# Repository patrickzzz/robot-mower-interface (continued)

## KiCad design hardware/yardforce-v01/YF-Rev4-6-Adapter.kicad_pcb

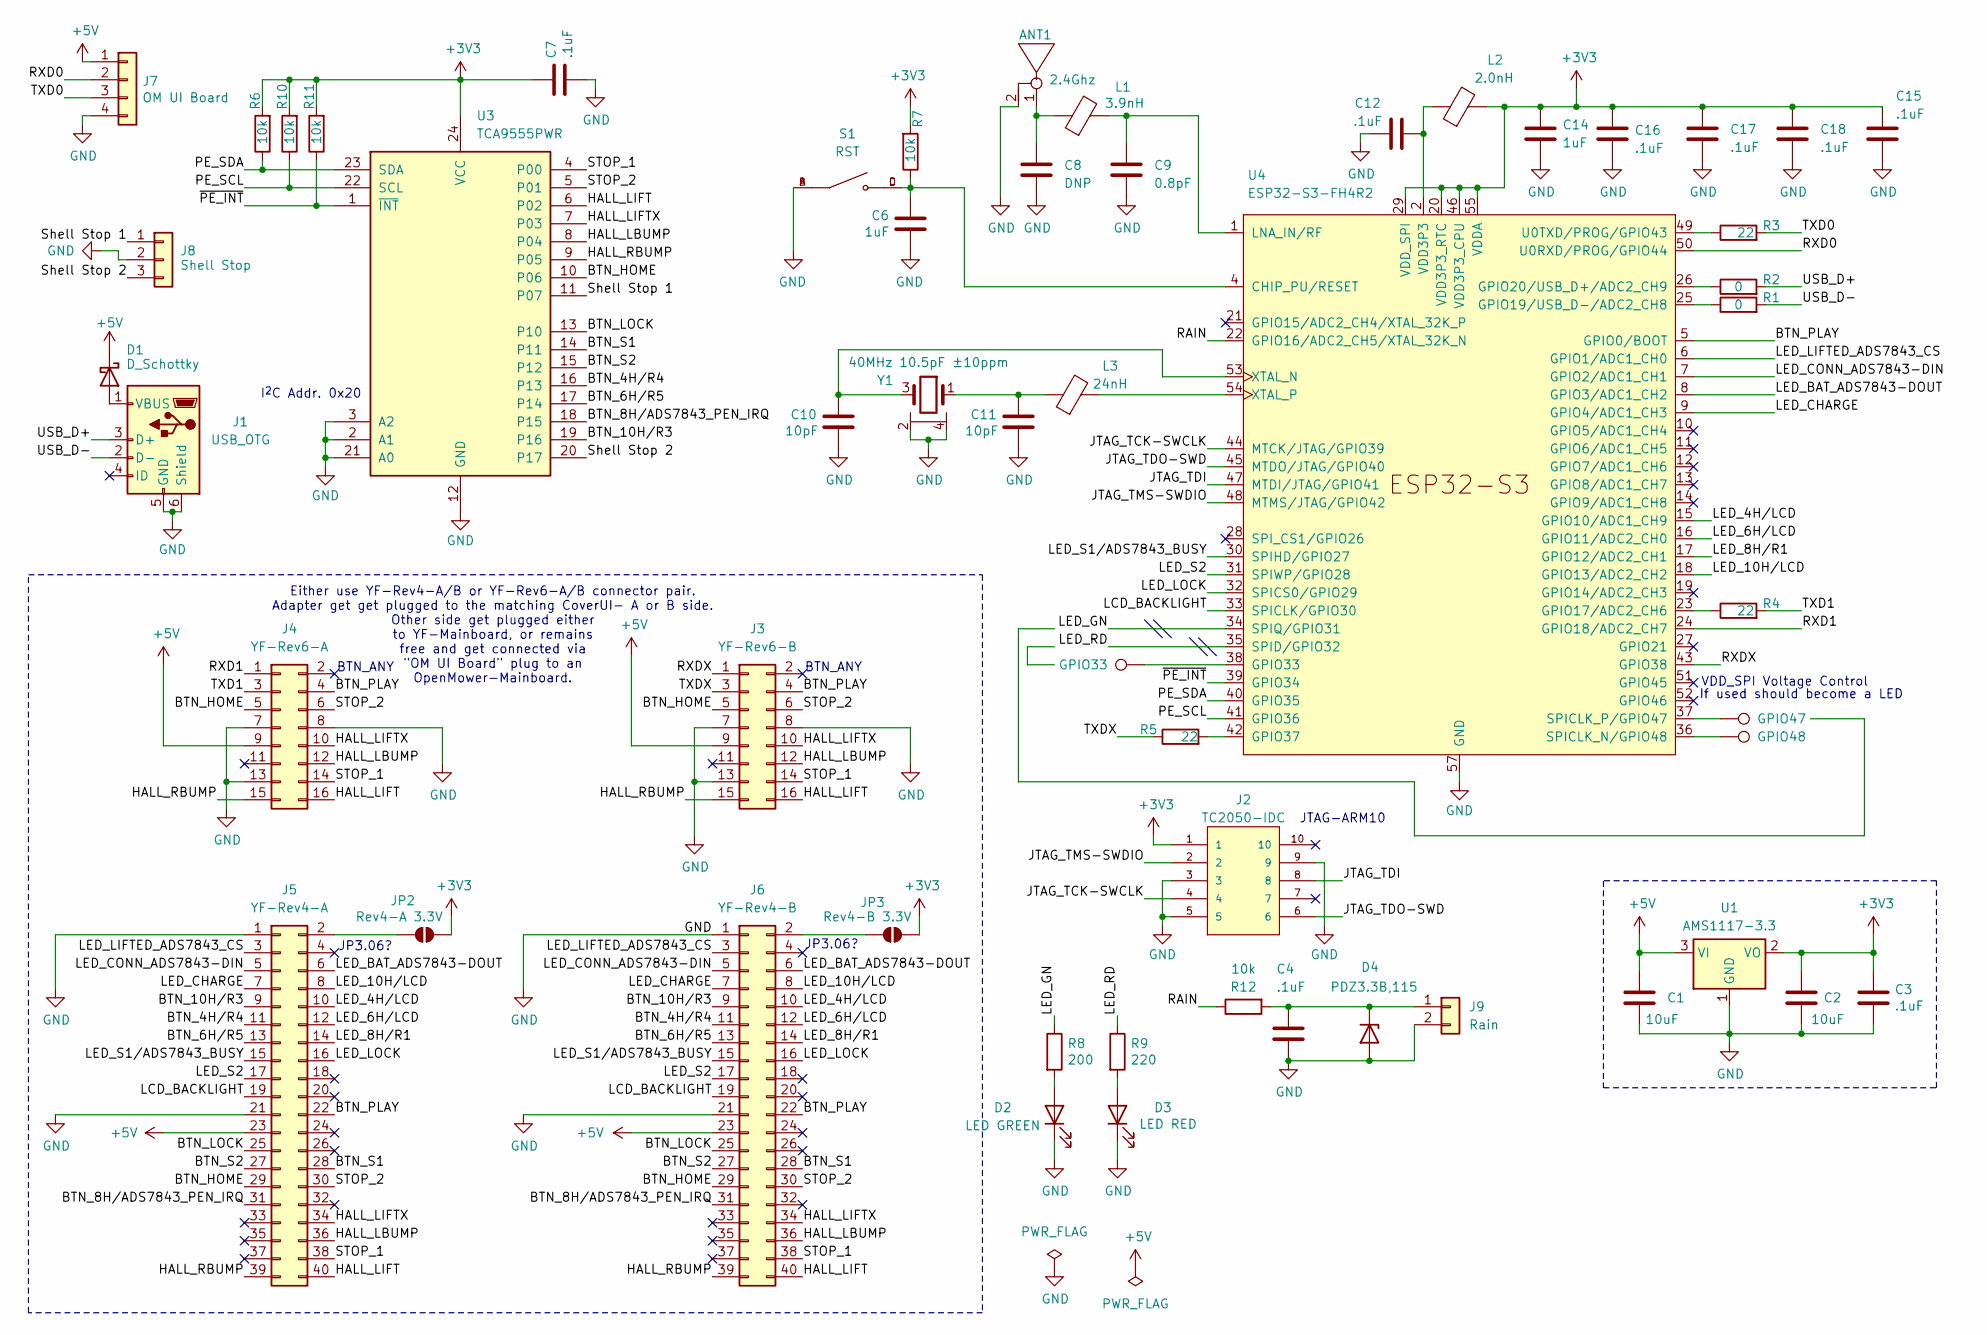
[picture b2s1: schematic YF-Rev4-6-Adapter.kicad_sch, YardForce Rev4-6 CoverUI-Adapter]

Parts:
ANT1: 2.4Ghz; PCB_Antenna_2.4GHz_Left
C1, C2: 10uF; C_0603_1608Metric; LCSC C19702
C3, C7, C12, C15, C16, C17, C18: .1uF; C_0402_1005Metric; LCSC C1525
C4: .1uF; C_0402_1005Metric; JLC C307331
C6, C14: 1uF; C_0402_1005Metric; LCSC C52923
C8: DNP; C_0402_1005Metric
C9: 0.8pF; C_0402_1005Metric; LCSC C5448872
C10, C11: 10pF; C_0402_1005Metric; MFR Part 0402CG140J500NT; LCSC C32949
D1: D_Schottky; D_SOD-123; Part Number PMEG2010ER,115; Digikey 1727-5192-1-ND
D2: LED GREEN; LED_0603_1608Metric; Part Number LTST-C191KGKT; Digikey 160-1446-1-ND
D3: LED RED; LED_0603_1608Metric; Part Number LTST-C191KRKT; Digikey 160-1447-1-ND
D4: PDZ3.3B,115; D_SOD-323; JLC C426855
GPIO33, GPIO47, GPIO48: TestPoint; TestPoint_Pad_1.0x1.0mm
J1: USB_OTG; USB_Micro-B_Wuerth_614105150721_Vertical; LCSC C668588
J2: TC2050-IDC; TAG-CONNECT_TC2050-IDC; PARTREV A
J3: YF-Rev6-B; IDC-Hybrid_2x08_P2.54mm_Latch_Vertical; DigiKey S9196-ND
J4: YF-Rev6-A; IDC-Hybrid_2x08_P2.54mm_Latch_Vertical; DigiKey S9196-ND
J5: YF-Rev4-A; IDC-Hybrid_2x20_P2.54mm_Latch_Vertical; DigiKey SFH11-PBPC-D20-ST-BK
J6: YF-Rev4-B; IDC-Hybrid_2x20_P2.54mm_Latch_Vertical; DigiKey SFH11-PBPC-D20-ST-BK
J7: OM UI Board; JST_XH_B4B-XH-A_1x04_P2.50mm_Vertical; Part Number B4B-XH-A(LF)(SN); Digikey 455-2249-ND
J8: Shell Stop; JST_XH_B3B-XH-A_1x03_P2.50mm_Vertical; Part Number B3B-XH-A(LF)(SN); LCSC C144394
J9: Rain; JST_XH_B2B-XH-A_1x02_P2.50mm_Vertical; Part Number B2B-XH-A-GU; Digikey 455-2946-ND
JP2: Rev4-A 3.3V; SolderJumper-2_P1.3mm_Open_RoundedPad1.0x1.5mm
JP3: Rev4-B 3.3V; SolderJumper-2_P1.3mm_Open_RoundedPad1.0x1.5mm
L1: 3.9nH; L_0402_1005Metric; LCSC C370223
L2: 2.0nH; L_0402_1005Metric; LCSC C963978
L3: 24nH; L_0402_1005Metric; MFR Part SDCL1005C24NJTDF; LCSC C401493
R1, R2: 0; R_0402_1005Metric; LCSC C17168
R3, R4, R5: 22; R_0603_1608Metric; LCSC C23345
R6, R7, R10, R11: 10k; R_0603_1608Metric; LCSC C25804
R8: 200; R_0603_1608Metric; LCSC C8218
R9: 220; R_0603_1608Metric; LCSC C22962
R12: 10k; R_0603_1608Metric; JLC C25744
S1: RST; SW_TS-1187A-B-A-B; PARTREV A0; LCSC C318884
U1: AMS1117-3.3; SOT-223-3_TabPin2; LCSC C6186
U3: TCA9555PWR; TSSOP-24_4.4x7.8mm_P0.65mm; LCSC C465732
U4: ESP32-S3-FH4R2; QFN-56-1EP_7x7mm_P0.4mm_EP4x4mm_ThermalVias; LCSC C3013940
Y1: 40MHz 10.5pF ±10ppm; Crystal_SMD_2016-4Pin_2.0x1.6mm; MF Part K2B4000010510; LCSC C18209006

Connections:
+3V3: C2.1, C3.1, C7.1, C14.1, C15.1, C16.1, C17.1, C18.1, J2.1, JP2.2 (B), JP3.2 (B), L2.2, R6.2, R7.2, R10.2, R11.2, U1.2 (VO), U3.24 (VCC), U4.20 (VDD3P3_RTC), U4.29 (VDD_SPI), U4.46 (VDD3P3_CPU), U4.55 (VDDA), U4.56 (VDDA)
+5V: C1.1, D1.1 (K), J3.9, J4.9, J5.23, J6.23, J7.1, U1.3 (VI)
/BTN_4H/R4: J5.11, J6.11, U3.16 (P13)
/BTN_6H/R5: J5.13, J6.13, U3.17 (P14)
/BTN_8H/ADS7843_PEN_IRQ: J5.31, J6.31, U3.18 (P15)
/BTN_10H/R3: J5.9, J6.9, U3.19 (P16)
/BTN_HOME: J3.5, J4.5, J5.29, J6.29, U3.10 (P06)
/BTN_LOCK: J5.25, J6.25, U3.13 (P10)
/BTN_PLAY: J3.4, J4.4, J5.22, J6.22, U4.5 (GPIO0/BOOT)
/BTN_S1: J5.28, J6.28, U3.14 (P11)
/BTN_S2: J5.27, J6.27, U3.15 (P12)
/HALL_LBUMP: J3.12, J4.12, J5.36, J6.36, U3.8 (P04)
/HALL_LIFT: J3.16, J4.16, J5.40, J6.40, U3.6 (P02)
/HALL_LIFTX: J3.10, J4.10, J5.34, J6.34, U3.7 (P03)
/HALL_RBUMP: J3.15, J4.15, J5.39, J6.39, U3.9 (P05)
/JTAG_TCK-SWCLK: J2.4, U4.44 (MTCK/JTAG/GPIO39)
/JTAG_TDI: J2.8, U4.47 (MTDI/JTAG/GPIO41)
/JTAG_TDO-SWD: J2.6, U4.45 (MTDO/JTAG/GPIO40)
/JTAG_TMS-SWDIO: J2.2, U4.48 (MTMS/JTAG/GPIO42)
/LCD_BACKLIGHT: J5.19, J6.19, U4.33 (SPICLK/GPIO30)
/LED_4H/LCD: J5.10, J6.10, U4.15 (GPIO10/ADC1_CH9)
/LED_6H/LCD: J5.12, J6.12, U4.16 (GPIO11/ADC2_CH0)
/LED_8H/R1: J5.14, J6.14, U4.17 (GPIO12/ADC2_CH1)
/LED_10H/LCD: J5.8, J6.8, U4.18 (GPIO13/ADC2_CH2)
/LED_BAT_ADS7843-DOUT: J5.6, J6.6, U4.8 (GPIO3/ADC1_CH2)
/LED_CHARGE: J5.7, J6.7, U4.9 (GPIO4/ADC1_CH3)
/LED_CONN_ADS7843-DIN: J5.5, J6.5, U4.7 (GPIO2/ADC1_CH1)
/LED_GN: R8.1, U4.34 (SPIQ/GPIO31)
/LED_LIFTED_ADS7843_CS: J5.3, J6.3, U4.6 (GPIO1/ADC1_CH0)
/LED_LOCK: J5.16, J6.16, U4.32 (SPICS0/GPIO29)
/LED_RD: R9.1, U4.35 (SPID/GPIO32)
/LED_S1/ADS7843_BUSY: J5.15, J6.15, U4.30 (SPIHD/GPIO27)
/LED_S2: J5.17, J6.17, U4.31 (SPIWP/GPIO28)
/PE_SCL: R10.1, U3.22 (SCL), U4.41 (GPIO36)
/PE_SDA: R6.1, U3.23 (SDA), U4.40 (GPIO35)
/RAIN: R12.1, U4.22 (GPIO16/ADC2_CH5/XTAL_32K_N)
/RXD0: J7.2, U4.50 (U0RXD/PROG/GPIO44)
/RXD1: J4.1, U4.24 (GPIO18/ADC2_CH7)
/RXDX: J3.1, U4.43 (GPIO38)
/STOP_1: J3.14, J4.14, J5.38, J6.38, U3.4 (P00)
/STOP_2: J3.6, J4.6, J5.30, J6.30, U3.5 (P01)
/Shell Stop 1: J8.1, U3.11 (P07)
/Shell Stop 2: J8.3, U3.20 (P17)
/TXD0: J7.3, R3.2
/TXD1: J4.3, R4.2
/TXDX: J3.3, R5.1
/USB_D+: J1.3 (D+), R2.2
/USB_D-: J1.2 (D-), R1.2
/~PE_INT: R11.1, U3.1 (~INT), U4.39 (GPIO34)
GND: ANT1.2, C1.2, C2.2, C3.2, C4.2, C6.2, C7.2, C8.2, C9.2, C10.2, C11.2, C12.1, C14.2, C15.2, C16.2, C17.2, C18.2, D2.1 (K), D3.1 (K), D4.2 (A), J1.5 (GND), J1.6 (Shield), J2.3, J2.5, J2.9, J3.7, J3.8, J3.13, J4.7, J4.8, J4.13, J5.1, J5.21, J6.1, J6.21, J7.4, J8.2, J9.2, S1.A, S1.B, U1.1 (GND), U3.2 (A1), U3.3 (A2), U3.12 (GND), U3.21 (A0), U4.57 (GND), Y1.2, Y1.4
unnamed: ANT1.1, C8.1, L1.1
unnamed: C11.1, L3.1, Y1.1
unnamed: D1.2 (A), J1.1 (VBUS)
unnamed: D2.2 (A), R8.2
unnamed: D3.2 (A), R9.2
unnamed: C4.1, D4.1 (K), J9.1, R12.2
unnamed: J5.2, JP2.1 (A)
unnamed: J6.2, JP3.1 (A)
unnamed: C6.1, R7.1, S1.C, S1.D, U4.4 (CHIP_PU/RESET)
unnamed: R4.1, U4.23 (GPIO17/ADC2_CH6)
unnamed: R1.1, U4.25 (GPIO19/USB_D-/ADC2_CH8)
unnamed: R2.1, U4.26 (GPIO20/USB_D+/ADC2_CH9)
unnamed: GPIO33.1, U4.38 (GPIO33)
unnamed: R5.2, U4.42 (GPIO37)
unnamed: C9.1, L1.2, U4.1 (LNA_IN/RF)
unnamed: GPIO48.1, U4.36 (SPICLK_N/GPIO48)
unnamed: GPIO47.1, U4.37 (SPICLK_P/GPIO47)
unnamed: R3.1, U4.49 (U0TXD/PROG/GPIO43)
unnamed: C10.1, U4.53 (XTAL_N), Y1.3
unnamed: L3.2, U4.54 (XTAL_P)
VDD3P3: C12.2, L2.1, U4.2 (VDD3P3), U4.3 (VDD3P3)

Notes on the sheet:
VDD_SPI Voltage Control
If used should become a LED
JTAG-ARM10
BTN_ANY
JP3.06?
Either use YF-Rev4-A/B or YF-Rev6-A/B connector pair. Adapter get get plugged to the matching CoverUI- A or B side. Other side get plugged either to YF-Mainboard, or remains free and get connected via "OM UI Board" plug to an OpenMower-Mainboard.
I^{2}C Addr. 0x20

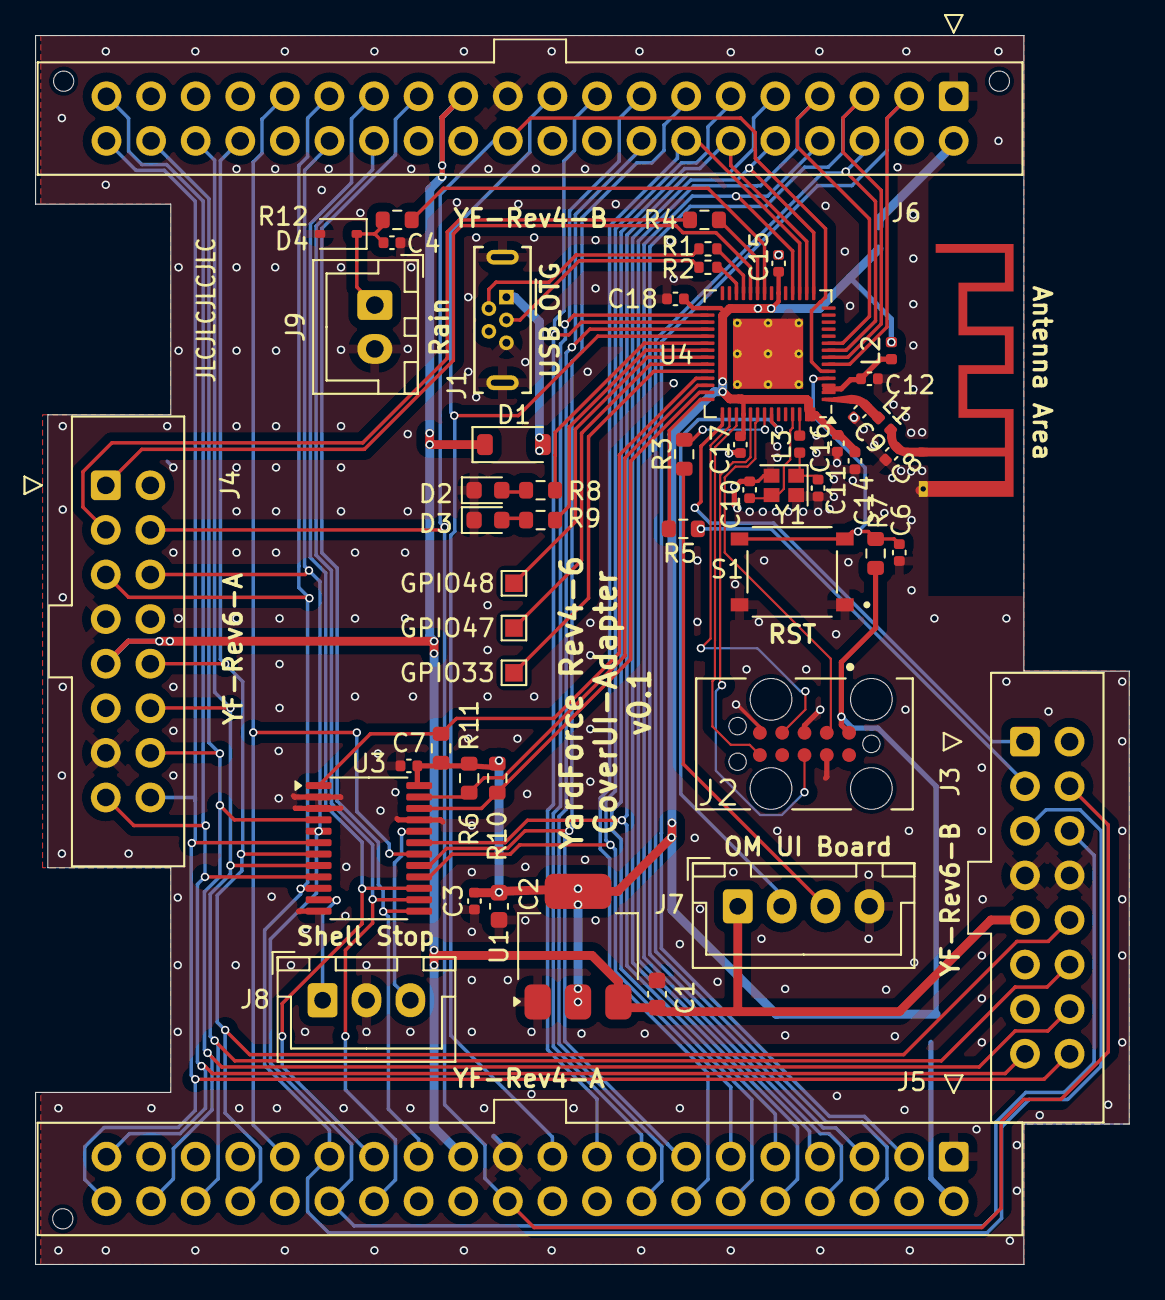
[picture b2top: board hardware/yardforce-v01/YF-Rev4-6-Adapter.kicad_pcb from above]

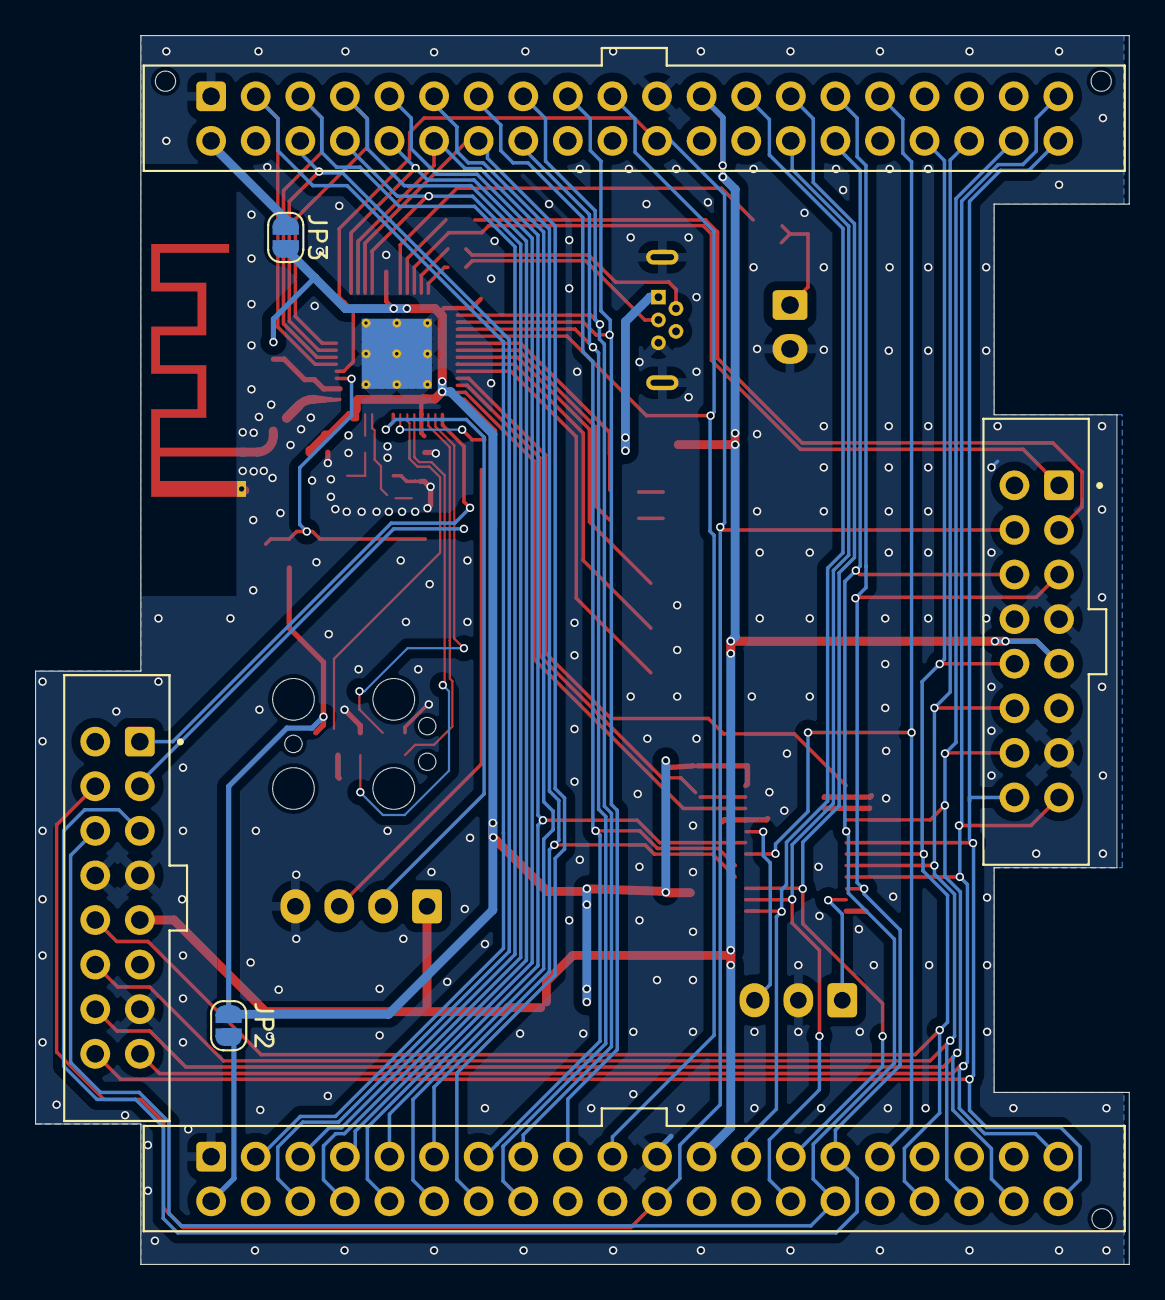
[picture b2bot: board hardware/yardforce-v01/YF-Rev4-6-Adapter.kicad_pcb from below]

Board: 2 copper layers, 62.3 x 70.0 mm, 55 parts (2 on the bottom side), 71 nets.

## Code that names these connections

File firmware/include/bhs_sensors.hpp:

/* Created by Apehaenger on 2024-12-02.
 * Copyright (c) 2024 Jörg Ebeling. All rights reserved.
 *
 * This file is part of the robot-interface project at https://github.com/patrickzzz/robot-interface.
 *
 * This work is licensed under a Creative Commons Attribution-NonCommercial-ShareAlike 4.0 International License.
 *
 * Feel free to use the design in your private/educational projects, but don't try to sell the design or products based on it without getting our consent first.
 *
 * THE SOFTWARE IS PROVIDED "AS IS", WITHOUT WARRANTY OF ANY KIND, EXPRESS OR
 * IMPLIED, INCLUDING BUT NOT LIMITED TO THE WARRANTIES OF MERCHANTABILITY,
 * FITNESS FOR A PARTICULAR PURPOSE AND NONINFRINGEMENT. IN NO EVENT SHALL THE
 * AUTHORS OR COPYRIGHT HOLDERS BE LIABLE FOR ANY CLAIM, DAMAGES OR OTHER
 * LIABILITY, WHETHER IN AN ACTION OF CONTRACT, TORT OR OTHERWISE, ARISING FROM,
 * OUT OF OR IN CONNECTION WITH THE SOFTWARE OR THE USE OR OTHER DEALINGS IN THE
 * SOFTWARE.
 */
#pragma once

#include <esp_log.h>
#include <freertos/queue.h>
#include <inttypes.h>

#include "config.h"
#include "esp_io_expander_tca95xx_16bit/include/esp_io_expander_tca95xx_16bit.h"
#include "I2CManager.hpp"
#include "pins.h"

extern LedSequencer led_red_seq;

/**
 * @brief Button-Hall-Switch Sensors, handle all of those input sensors like:
 * - User Button on the CoverUI
 * - Hall Switches connected to the CoverUI
 * - Normal switches like Stop-Switches on the CoverUI or the Adapter-PCB
 *
 * All input signals get debounced before processed!
 */
namespace bhs_sensors {

// For efficiency and simplicity port expanders input value get assigned 1:1 to a bitfields struct (+ the mapped GPIO play button)
struct State {
#ifdef HW_0_1_X
    bool stop_1 : 1;        // 2 pin plug @ CoverUI. Fit with back-handle plug of one side
    bool stop_2 : 1;        // 2 pin plug @ CoverUI. Fit with back-handle plug of the other side
    bool lift : 1;          // Hall (lift) sensor
    bool lift_x : 1;        // Hall (lift2) sensor
    bool bump_l : 1;        // Hall (bumper) sensor
    bool bump_r : 1;        // Hall (bumper2) sensor
    bool btn_home : 1;      // CoverUI button
    bool shell_stop_1 : 1;  // Shell Stop Plug J8 (pin 1-2) on adapter PCB
    bool btn_lock : 1;      // CoverUI button
    bool btn_s1 : 1;        // CoverUI button
    bool btn_s2 : 1;        // CoverUI button
    // Same as with the "hr" LEDs. If a CoverUI has "hr" buttons, it has 4 of them, but their value is model specific
    bool btn_hr_14 : 1;     // CoverUI button
    bool btn_hr_24 : 1;     // CoverUI button
    bool btn_hr_34 : 1;     // CoverUI button
    bool btn_hr_44 : 1;     // CoverUI button
    bool shell_stop_2 : 1;  // Shell Stop Plug J8 (pin 2-3) on adapter PCB
    // GPIO button inputs get MSB prefixed to TCA9555 inputs
    bool btn_play : 1;  // CoverUI button
#elif HW_0_2_X
    bool stop_2 : 1;        // 2 pin plug @ CoverUI. Fit with back-handle plug of the other side
    bool lift_x : 1;        // Hall (lift2) sensor
    bool bump_l : 1;        // Hall (bumper) sensor
    bool stop_1 : 1;        // 2 pin plug @ CoverUI. Fit with back-handle plug of one side
    bool bump_r : 1;        // Hall (bumper2) sensor
    bool lift : 1;          // Hall (lift) sensor
    bool shell_stop_1 : 1;  // Shell Stop Plug J8 (pin 1-2) on adapter PCB
    bool shell_stop_2 : 1;  // Shell Stop Plug J8 (pin 2-3) on adapter PCB
    // Same as with the "hr" LEDs. If a CoverUI has "hr" buttons, it has 4 of them, but their value is model specific
    bool btn_hr_14 : 1;   // CoverUI button
    bool btn_hr_24 : 1;   // CoverUI button
    bool btn_hr_34 : 1;   // CoverUI button
    bool btn_hr_44 : 1;   // CoverUI button
    bool btn_lock : 1;    // CoverUI button
    bool btn_s2 : 1;      // CoverUI button
    bool btn_s1 : 1;      // CoverUI button
    bool btn_unused : 1;  // Unused TCA input
    // GPIO button inputs get MSB prefixed to TCA9555 inputs
    bool btn_play : 1;  // CoverUI button
    bool btn_home : 1;  // CoverUI button
#else
#error No hardware version HW_x_y_z defined
#endif
};

const char *TAG = "bhs_sensors";

// A typical bounce time is between 2ms up to 10ms.
// To be on the save side, the result of taskCycle * numDebounceStates should be larger
constexpr TickType_t taskCycle = 5;
constexpr uint8_t numDebounceStates = 6;

namespace {  // Anonymous private namespace

// Port expander vars
//static i2c_master_bus_handle_t i2c_handle_ = NULL;
static esp_io_expander_handle_t io_expander_ = NULL;

// BHS states
union StateU {
    uint32_t raw;
    State state;
};
static StateU state_debounced_;  // Current state of debounced BHS sensors

}  // namespace

/**
 * @brief Initialize GPIOs and I2C interfaces
 *
 * @return esp_err_t
 */
esp_err_t init(SystemHealth &sys_health) {
    ESP_LOGI(TAG, "init()");

/*
    // Init I2C for TCA9555 port expander
    const i2c_master_bus_config_t bus_config = {
        .i2c_port = I2C_NUM_0,
        .sda_io_num = portExpSDA,
        .scl_io_num = portExpSCL,
        .clk_source = I2C_CLK_SRC_DEFAULT,
        .glitch_ignore_cnt = 7,
        .intr_priority = 0,
        .trans_queue_depth = 0,
        .flags = {.enable_internal_pullup = 1}};
    if (esp_err_t ret = i2c_new_master_bus(&bus_config, &i2c_handle_) != ESP_OK) {
        ESP_LOGW(TAG, "I2C init failed with error: %s", esp_err_to_name(ret));
        return ret;
    }
    sys_health.port_expander_i2c = true;

    // Init TCA9555 port expander
    if (esp_err_t ret = esp_io_expander_new_i2c_tca95xx_16bit(i2c_handle_, ESP_IO_EXPANDER_I2C_TCA9555_ADDRESS_000, &io_expander_) != ESP_OK) {
        ESP_LOGW(TAG, "Port expander connect failed with error: %s", esp_err_to_name(ret));
        return ret;
    }

    if (esp_err_t ret = esp_io_expander_set_dir(io_expander_, portExpBtnPinMask, IO_EXPANDER_INPUT) != ESP_OK) {
        ESP_LOGW(TAG, "Port expander 'set direction' failed with error: %s", esp_err_to_name(ret));
        return ret;
    }

 */
    io_expander_ = I2CManager::getInstance().getIoExpander();
    sys_health.port_expander = true;

    esp_io_expander_print_state(io_expander_);

    // Play button on normal GPIO
    gpio_config_t gpio_conf = {
        .pin_bit_mask = (1ULL << pinButtonPlay),
        .mode = GPIO_MODE_INPUT,
        .pull_up_en = GPIO_PULLUP_ENABLE,
        .pull_down_en = GPIO_PULLDOWN_DISABLE,
        .intr_type = GPIO_INTR_DISABLE};
    gpio_config(&gpio_conf);

    return ESP_OK;
}

/**
 * @brief Return (debounced) State bitfield for any button, hall or switch.
 * @return State
 */
State getState() {
    return state_debounced_.state;
}

/**
 * @brief Has to get called regulary i.e. by timer or task (approx. 5ms).
 * Store the (button, hall and switch) GPIO states within states_ array and debounces em.
 */
void task(void *arg) {
    static uint32_t states_[numDebounceStates];  // GPIO port state recorder for every taskCycle time interval
    static uint8_t state_index_ = 0;             // Index for next states_ store positions
    // uint32_t state_changed_;                  // Just changed buttons. Might be used if button events are required

    while (1) {
        uint32_t val = 0;
        // Get port expander buttons
        if (esp_err_t ret = esp_io_expander_get_level(io_expander_, portExpBtnPinMask, &val) == ESP_OK) {
            states_[state_index_] = val ^ 0xffff;  // XOR for active-low buttons
        } else {
            led_red_seq.blink({.on_ms = 100, .off_ms = 100, .limit_blink_cycles = 1, .fulfill = true});  // One quick red flash indicate a communication error;
            ESP_LOGW(TAG, "Port expander read failed with error: %s", esp_err_to_name(ret));
        }

        // Add mergeable button(s)
#ifdef HW_0_1_X
        states_[state_index_] |= (gpio_get_level(pinButtonPlay) ? 0 : (uint32_t)mergedExpPinBtnPlay);
#elif HW_0_2_X
        states_[state_index_] |= (gpio_get_level(pinButtonPlay) ? 0 : (uint32_t)mergedExpPinBtnPlay) | (gpio_get_level(pinButtonHome) ? 0 : (uint32_t)mergedExpPinBtnHome);
#else
#error No hardware version HW_x_y_z defined
#endif

        // Debounce
        // uint32_t laststate_debounced_ = state_debounced_.raw;
        unsigned int i;
        for (i = 0, state_debounced_.raw = 0xffffffff; i < numDebounceStates; i++)
            state_debounced_.raw &= states_[i];

        /* AH20241204 Could be used for BHS event trigger of changed BHS sensors
        // Save what changed
        state_changed_ = state_debounced_ ^ laststate_debounced_.raw; */

        // Circular buffer index
        state_index_++;
        if (state_index_ >= numDebounceStates)
            state_index_ = 0;

        vTaskDelay(taskCycle / portTICK_PERIOD_MS);
    }
}

}  // namespace bhs_sensors

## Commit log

2024-10-27 Several changes for v0.2.0 (see CHANGELOG.md)
2024-10-28 Changes to avoid watchdog timer problems: serve static files gzip compressed + increase timeout
2024-10-28 New gzipped webinterface
2024-10-28 Automatically reconnect if Wifi connection is lost
2024-10-28 Ability to do Firmware updates over the air (OTA)
2024-11-03 Minor improvements
2024-11-11 Fix ERC issues
2024-11-12 Add Rev4 3V3 solder jumper
2024-11-12 Fix DRC issues
2024-11-12 BOM Update
2024-11-24 Add HW Prototype v0.1
2024-11-25 Change Micro-USB part to U255-051N-4BH70-SS
2024-11-25 Fix compile error
2024-12-04 Add test-prototype sandbox/example ESP-IDF code
2024-12-04 Add HW v0.1 files and manual mods
2024-12-06 Correct image names
2024-12-06 Finalization of test-prototype
2024-12-27 Don't truncate logs on every startup Correct loading of mowing plan on boot up
2024-12-28 Rev 0.2 hardware
2024-12-28 Add modes of operation overview
2024-12-28 Correct header
2025-01-13 Add mainboard-immitator based on ESP IDF for testing purposes
2025-01-14 Copy of test-prototype, containing a first class to speak to YF CoverUI
2025-01-15 Beginning of LED State manager class
2025-01-16 Add HW comment
2025-01-16 Add HW_0_2_X support for test-prototype
2025-01-16 Add UART pins and baud
2025-01-16 Release v0.2 prototype
2025-01-18 Test for 40 Pin
2025-01-18 initial commit of protoype 2 (wip)
2025-01-19 First PoC
2025-01-20 WIP, Start v2 hardware
2025-01-21 Current state, start of buttons support
2025-01-22 Add Button Handling + ButtonPress-Observer-Handling
2025-01-24 Branch Init and MainboardInterface PoC
2025-01-24 First button (lock) is set to button state from UART message
2025-01-24 UART read PoC, cleanup of main, complete destructors
2025-01-25 mainboards implementation cleanup
2025-01-25 Add/change license header
2025-01-25 COBS decoder seem to work
2025-01-25 COBS lib
2025-01-25 Add Halls / move debouncer to GPIO Controller
2025-01-25 Update state
2025-01-25 Example debugging button/hall event handler
2025-01-25 Finished COBS decoding, CRC validation and Set_LEDs OM packet
2025-01-25 Add PIO development ENVs
2025-01-26 Simplified error handling in init() and derived OM driver
2025-01-26 Add firmwareVersion (required for 'Get_Version' packet
2025-01-26 Add 'Get_Version' packet handling with response
2025-01-27 Fix COBS packet handling
2025-01-27 Add Get_Version info
2025-01-27 Added button handler to main
2025-01-27 Remove bhs_sensors
2025-01-28 First start of uart bridge for yf
2025-01-29 Update ESP32-S3 technical reference to newer version
2025-01-30 Correction of high/low status + Beginn of UARTEventObserver Interface
2025-01-31 Substitute vectors, some more other improvements
2025-02-03 Organisational changes: Added folders, renamed and moved classes
2025-02-03 For now, removed from lib and added to src
2025-02-05 New working state with YFVirtual + YFHardware Mainboard types
2025-02-07 First "Bridge" proposal which became a "EventBroker"
2025-02-10 Prepared HW v0.3
2025-02-10 Dependency for EvenBroker proposal
